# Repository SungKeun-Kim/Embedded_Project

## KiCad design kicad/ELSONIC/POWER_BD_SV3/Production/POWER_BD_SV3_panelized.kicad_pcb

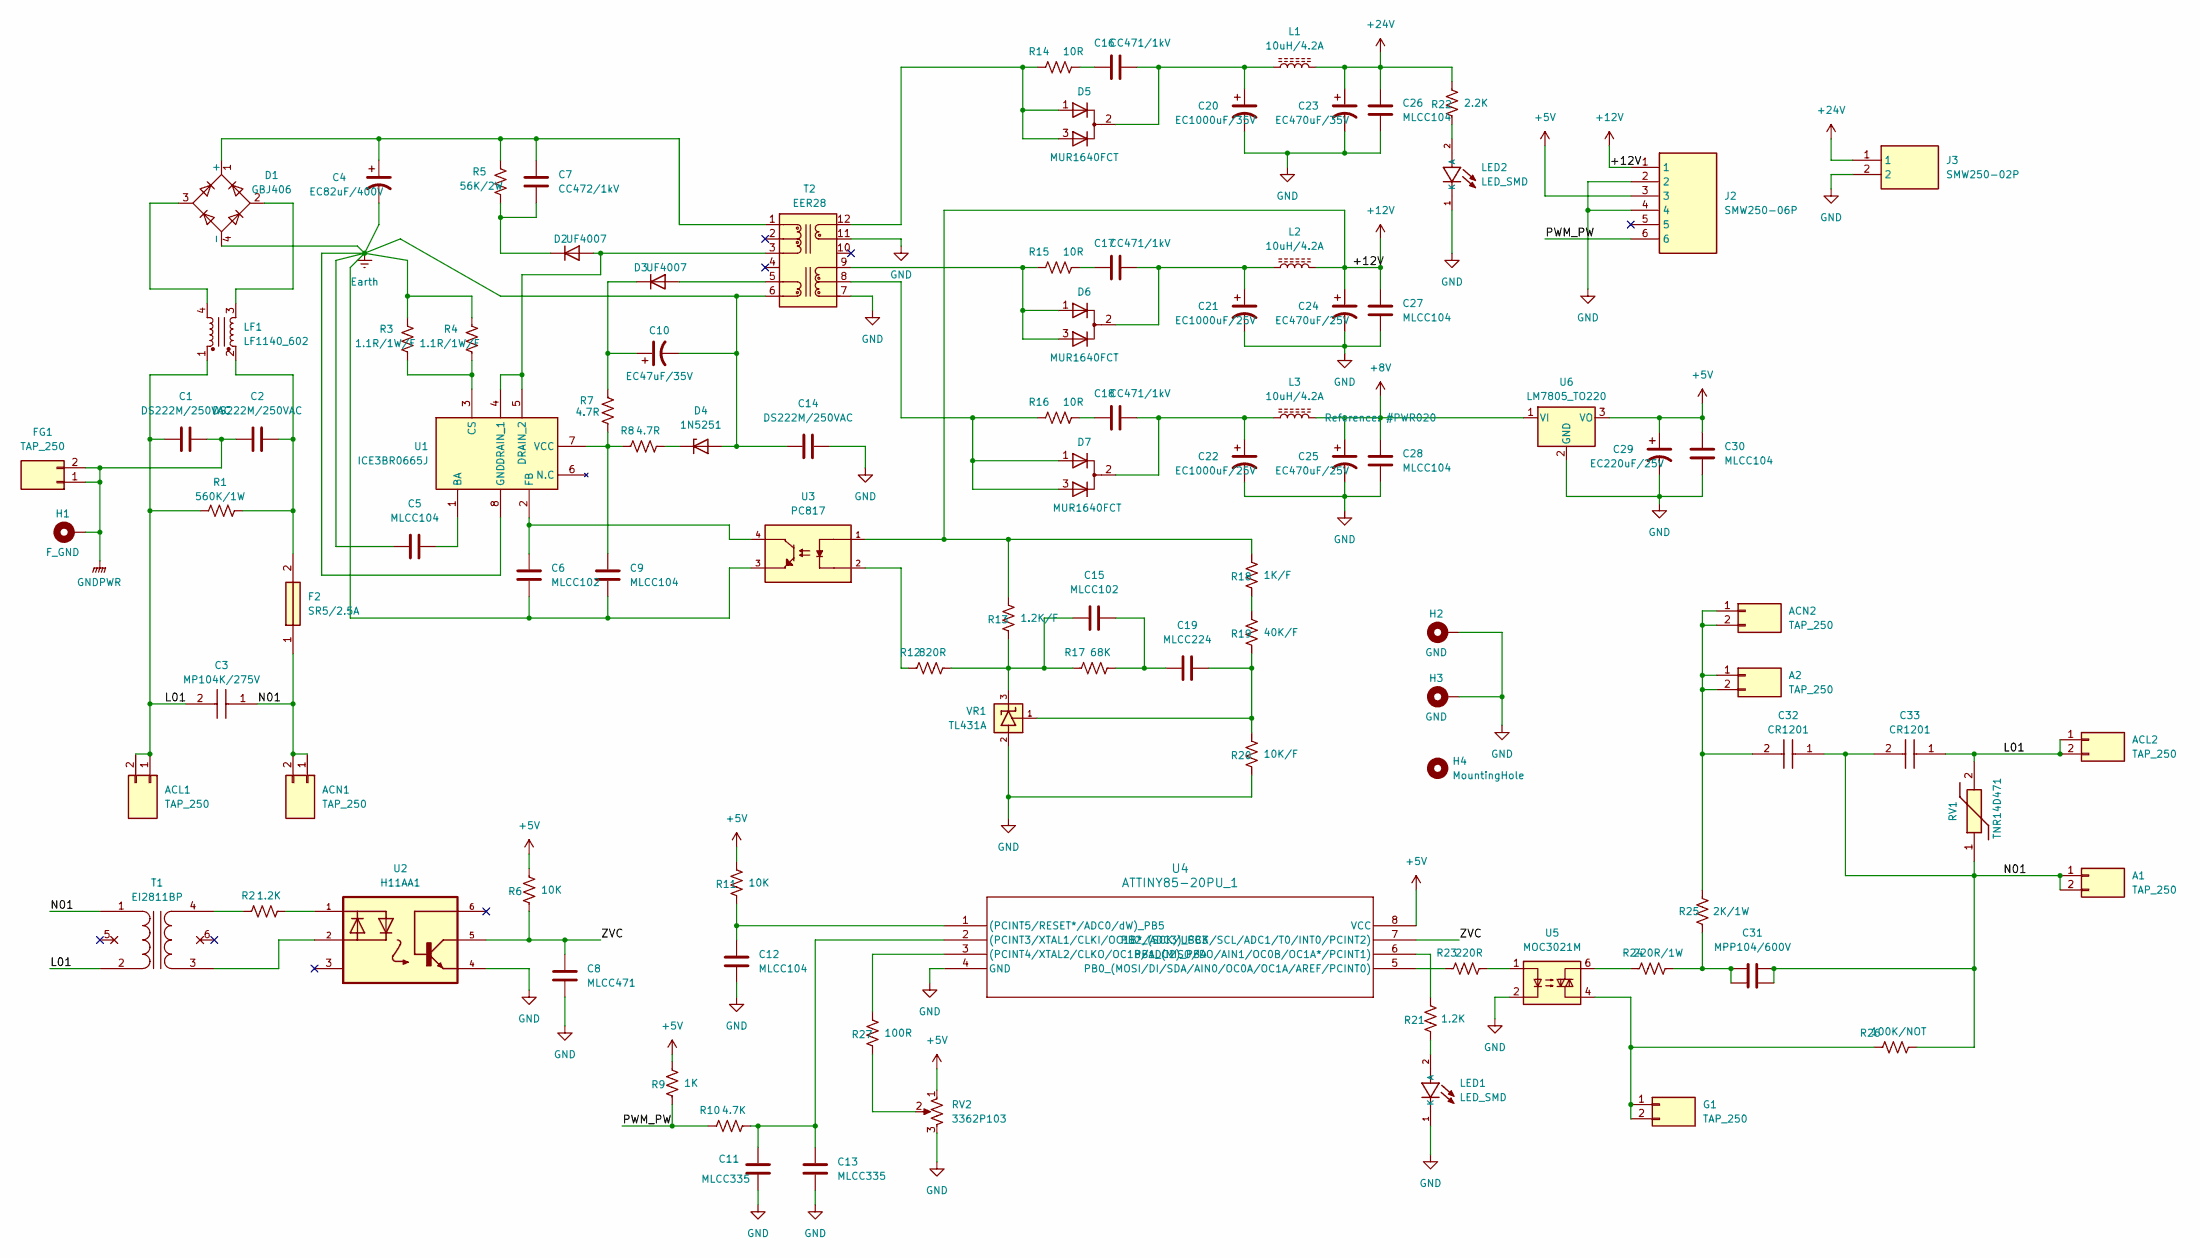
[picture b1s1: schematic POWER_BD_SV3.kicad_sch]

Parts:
A1, A2: TAP_250
ACL1, ACL2: TAP_250
ACN1, ACN2: TAP_250
C1, C2, C14: DS222M/250VAC; DS222M
C3: MP104K/275V; 104K_275V
C4: EC82uF/400V; 82uF_400V
C5, C9, C12, C26, C27, C28, C30: MLCC104; C_3216Metric
C6, C15: MLCC102; C_3216Metric
C7: CC472/1kV; C_Disc_D6.0mm_P5.00mm
C8: MLCC471; C_3216Metric
C10: EC47uF/35V; CP_Radial_D5.0mm_P2.00mm
C11, C13: MLCC335; C_3216Metric
C16, C17, C18: CC471/1kV; C_Disc_D4.7mm_P5.00mm
C19: MLCC224; C_3216Metric
C20: EC1000uF/35V; CP_Radial_D12.5mm_P5.00mm
C21, C22: EC1000uF/25V; CP_Radial_D10.0mm_P5.00mm
C23: EC470uF/35V; CP_Radial_D10.0mm_P5.00mm
C24, C25: EC470uF/25V; CP_Radial_D10.0mm_P5.00mm
C29: EC220uF/25V; CP_Radial_D6.3mm_P2.50mm
C31: MPP104/600V; C_PP_P10.0mm_P21.2mm
C32, C33: CR1201; SPARK_KILLER
D1: GBJ406
D2, D3: UF4007; Diode_P10.16mm
D4: 1N5251; ZENER_0_5W_P7.62mm_Hori
D5, D6, D7: MUR1640FCT; TO220AB_P2.55mm
F2: SR5/2.5A; SR525ABK
FG1: TAP_250
G1: TAP_250
H1: F_GND; MTHole_3.5mm_7.5mmPad_GND
H2, H3: GND; MTHole_3.5mm_7.5mmPad_GND
H4: MountingHole; MTHole_3.5mm
J2: SMW250-06P; SMW250_06P
J3: SMW250-02P; SMW250_02P
L1, L2, L3: 10uH/4.2A; L_Radial_D7.5mm_P3.50mm
LED1, LED2: LED_SMD; LED_2012Metric
LF1: LF1140_602; LF1140
R1: 560K/1W; R_Axial_1W_P14.6mm
R2, R21: 1.2K; R_3216Metric
R3, R4: 1.1R/1W/F; R_Axial_1W_P14.6mm
R5: 56K/2W; R_Axial_2W_P20.32mm
R6, R11: 10K; R_3216Metric
R7, R8: 4.7R; R_3216Metric
R9: 1K; R_3216Metric
R10: 4.7K; R_3216Metric
R12: 820R; R_3216Metric
R13: 1.2K/F; R_3216Metric
R14, R15, R16: 10R; R_3216Metric
R17: 68K; R_3216Metric
R18: 1K/F; R_3216Metric
R19: 40K/F; R_3216Metric
R20: 10K/F; R_3216Metric
R22: 2.2K; R_3216Metric
R23: 220R; R_3216Metric
R24: 220R/1W; R_Axial_1W_P14.6mm
R25: 2K/1W; R_Axial_1W_P14.6mm
R26: 100K/NOT; R_Axial_0.25W_P10.16mm
R27: 100R; R_3216Metric
RV1: TNR14D471; TNR14D_P7.62
RV2: 3362P103; TRIM_3362P
T1: EI2811BP
T2: EER28; EER28_35_12P
U1: ICE3BR0665J; DIP-8_W7.62mm_Socket
U2: H11AA1; DIP-6_W7.62mm
U3: PC817; DIP-4_W7.62mm_Socket
U4: ATTINY85-20PU_1; DIP-8_W7.62mm_Socket
U5: MOC3021M; DIP-6_W7.62mm
U6: LM7805_TO220; TO220_P2.54mm
VR1: TL431A; TO92_P2.5mm; PARTREV R

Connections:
+5V: C29.1, C30.2, J2.3, R6.2, R9.2, R11.2, RV2.1, U4.8 (VCC), U6.3 (VO)
+8V: C25.1, C28.2, L3.2, U6.1 (VI)
+12V: C24.1, C27.2, J2.1, L2.2, R13.2, R18.2, U3.1
+24V: C23.1, C26.2, J3.1, L1.2, R22.2
/L01: ACL1.1, ACL1.2, ACL2.1, ACL2.2, C1.1, C3.2, C33.1, LF1.1, R1.1, RV1.2, T1.2 (AB)
/N01: A1.1, A1.2, ACN1.1, ACN1.2, C3.1, C31.2, C31.4, C32.1, C33.2, F2.1, R26.2, RV1.1, T1.1 (AA)
/PWM_PW: J2.6, R9.1, R10.1
/ZVC: C8.2, R6.1, U2.5, U4.7 (PB2_(SCK/USCK/SCL/ADC1/T0/INT0/PCINT2))
Earth: C4.2, C5.1, C6.1, C9.1, C10.2, C14.1, D1.4 (-), D4.2 (A), R3.1, R4.1, T2.6 (Vcc_GND), U1.8 (GND), U3.3
GND: C8.1, C11.1, C12.1, C13.1, C14.2, C20.2, C21.2, C22.2, C23.2, C24.2, C25.2, C26.1, C27.1, C28.1, C29.2, C30.1, H2.1, H3.1, J2.2, J2.4, J3.2, LED1.1 (K), LED2.1 (K), R20.1, RV2.3, T2.7 (N_GND1), T2.11 (N_GND2), U2.4, U4.4 (GND), U5.2, U6.2 (GND), VR1.2
GNDPWR: C1.2, C2.1, FG1.1, FG1.2, H1.1
unnamed: A2.1, A2.2, ACN2.1, ACN2.2, C32.2, R25.1
unnamed: C2.2, F2.2, LF1.2, R1.2
unnamed: C15.1, R12.2, R13.1, R17.1, VR1.3
unnamed: C15.2, C19.1, R17.2
unnamed: C16.1, R14.2
unnamed: C17.1, R15.2
unnamed: C18.1, R16.2
unnamed: C19.2, R19.1, R20.2, VR1.1
unnamed: C31.1, C31.3, R24.2, R25.2
unnamed: C4.1, C7.1, D1.1 (+), R5.1, T2.1 (P0)
unnamed: D1.2, LF1.3
unnamed: D1.3, LF1.4
unnamed: D2.2 (A), T2.3 (P2), U1.4 (DRAIN_1), U1.5 (DRAIN_2)
unnamed: C7.2, D2.1 (K), R5.2
unnamed: D3.2 (A), T2.5 (Vcc)
unnamed: C10.1, D3.1 (K), R7.1
unnamed: D4.1 (K), R8.2
unnamed: C16.2, C20.1, D5.2 (K), L1.1
unnamed: C17.2, C21.1, D6.2 (K), L2.1
unnamed: C18.2, C22.1, D7.2 (K), L3.1
unnamed: G1.1, G1.2, R26.1, U5.4
unnamed: LED1.2 (A), R21.2
unnamed: LED2.2 (A), R22.1
unnamed: R2.2, U2.1
unnamed: R12.1, U3.2
unnamed: R18.1, R19.2
unnamed: R23.2, U5.1
unnamed: R24.1, U5.6
unnamed: R27.1, RV2.2
unnamed: T1.3 (SA), U2.2
unnamed: R2.1, T1.4 (SB)
unnamed: D7.1 (A), D7.3 (A), R16.1, T2.8 (N1)
unnamed: D6.1 (A), D6.3 (A), R15.1, T2.9 (N2)
unnamed: D5.1 (A), D5.3 (A), R14.1, T2.12 (N3)
unnamed: C5.2, U1.1 (BA)
unnamed: R3.2, R4.2, U1.3 (CS)
unnamed: C6.2, U1.2 (FB), U3.4
unnamed: C9.2, R7.2, R8.1, U1.7 (VCC)
unnamed: C11.2, C13.2, R10.2, U4.2 ((PCINT3/XTAL1/CLKI/OC1B*/ADC3)_PB3)
unnamed: R27.2, U4.3 ((PCINT4/XTAL2/CLKO/OC1B/ADC2)_PB4)
unnamed: C12.2, R11.1, U4.1 ((PCINT5/RESET*/ADC0/dW)_PB5)
unnamed: R23.1, U4.5 (PB0_(MOSI/DI/SDA/AIN0/OC0A/OC1A/AREF/PC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)
unnamed: R21.1, U4.6 (PB1_(MISO/DO/AIN1/OC0B/OC1A*/PCINT1))

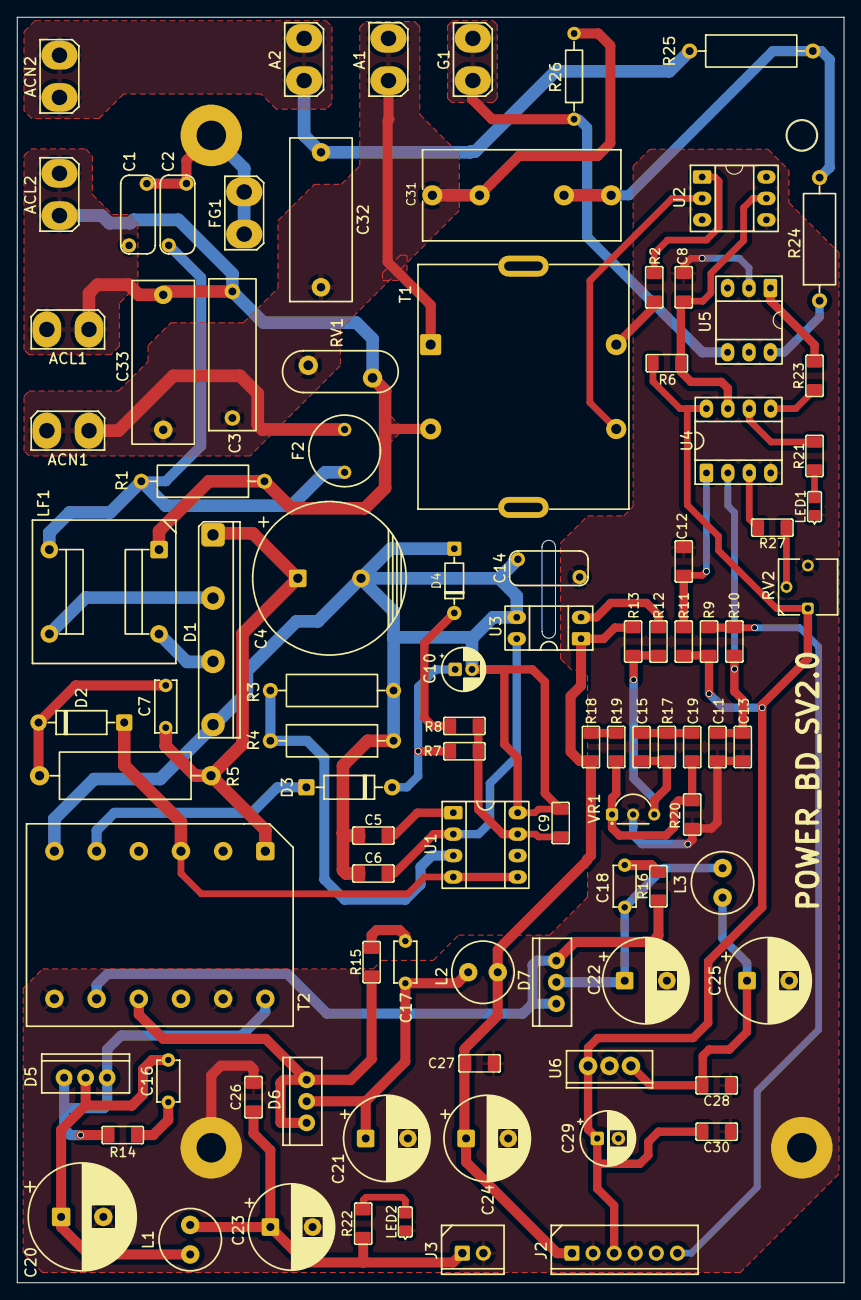
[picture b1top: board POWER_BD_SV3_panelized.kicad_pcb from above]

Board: 2 copper layers, 98.0 x 150.0 mm, 99 parts (0 on the bottom side), 54 nets.
